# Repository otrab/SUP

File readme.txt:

Readme

Current on HDMI 5v line
http://forum.xda-developers.com/showthread.php?t=2384480

HDMI specification
https://en.wikipedia.org/wiki/HDMI
http://www.hdmi.org/installers/insidehdmicable.aspx

Great ideas
http://forum.arduino.cc/index.php?topic=119879.0
http://articulo.mercadolibre.cl/MLC-432821282-switch-hdmi-hasta-3-dispositivos-1080p-_JM ($4.800)
http://www.aliexpress.com/item/1pc-Switcher-Splitter-Cable-For-HDTV-3-IN-1-OUT-1080P-Hub-V1-4B-HDMI-Switch/32291909706.html

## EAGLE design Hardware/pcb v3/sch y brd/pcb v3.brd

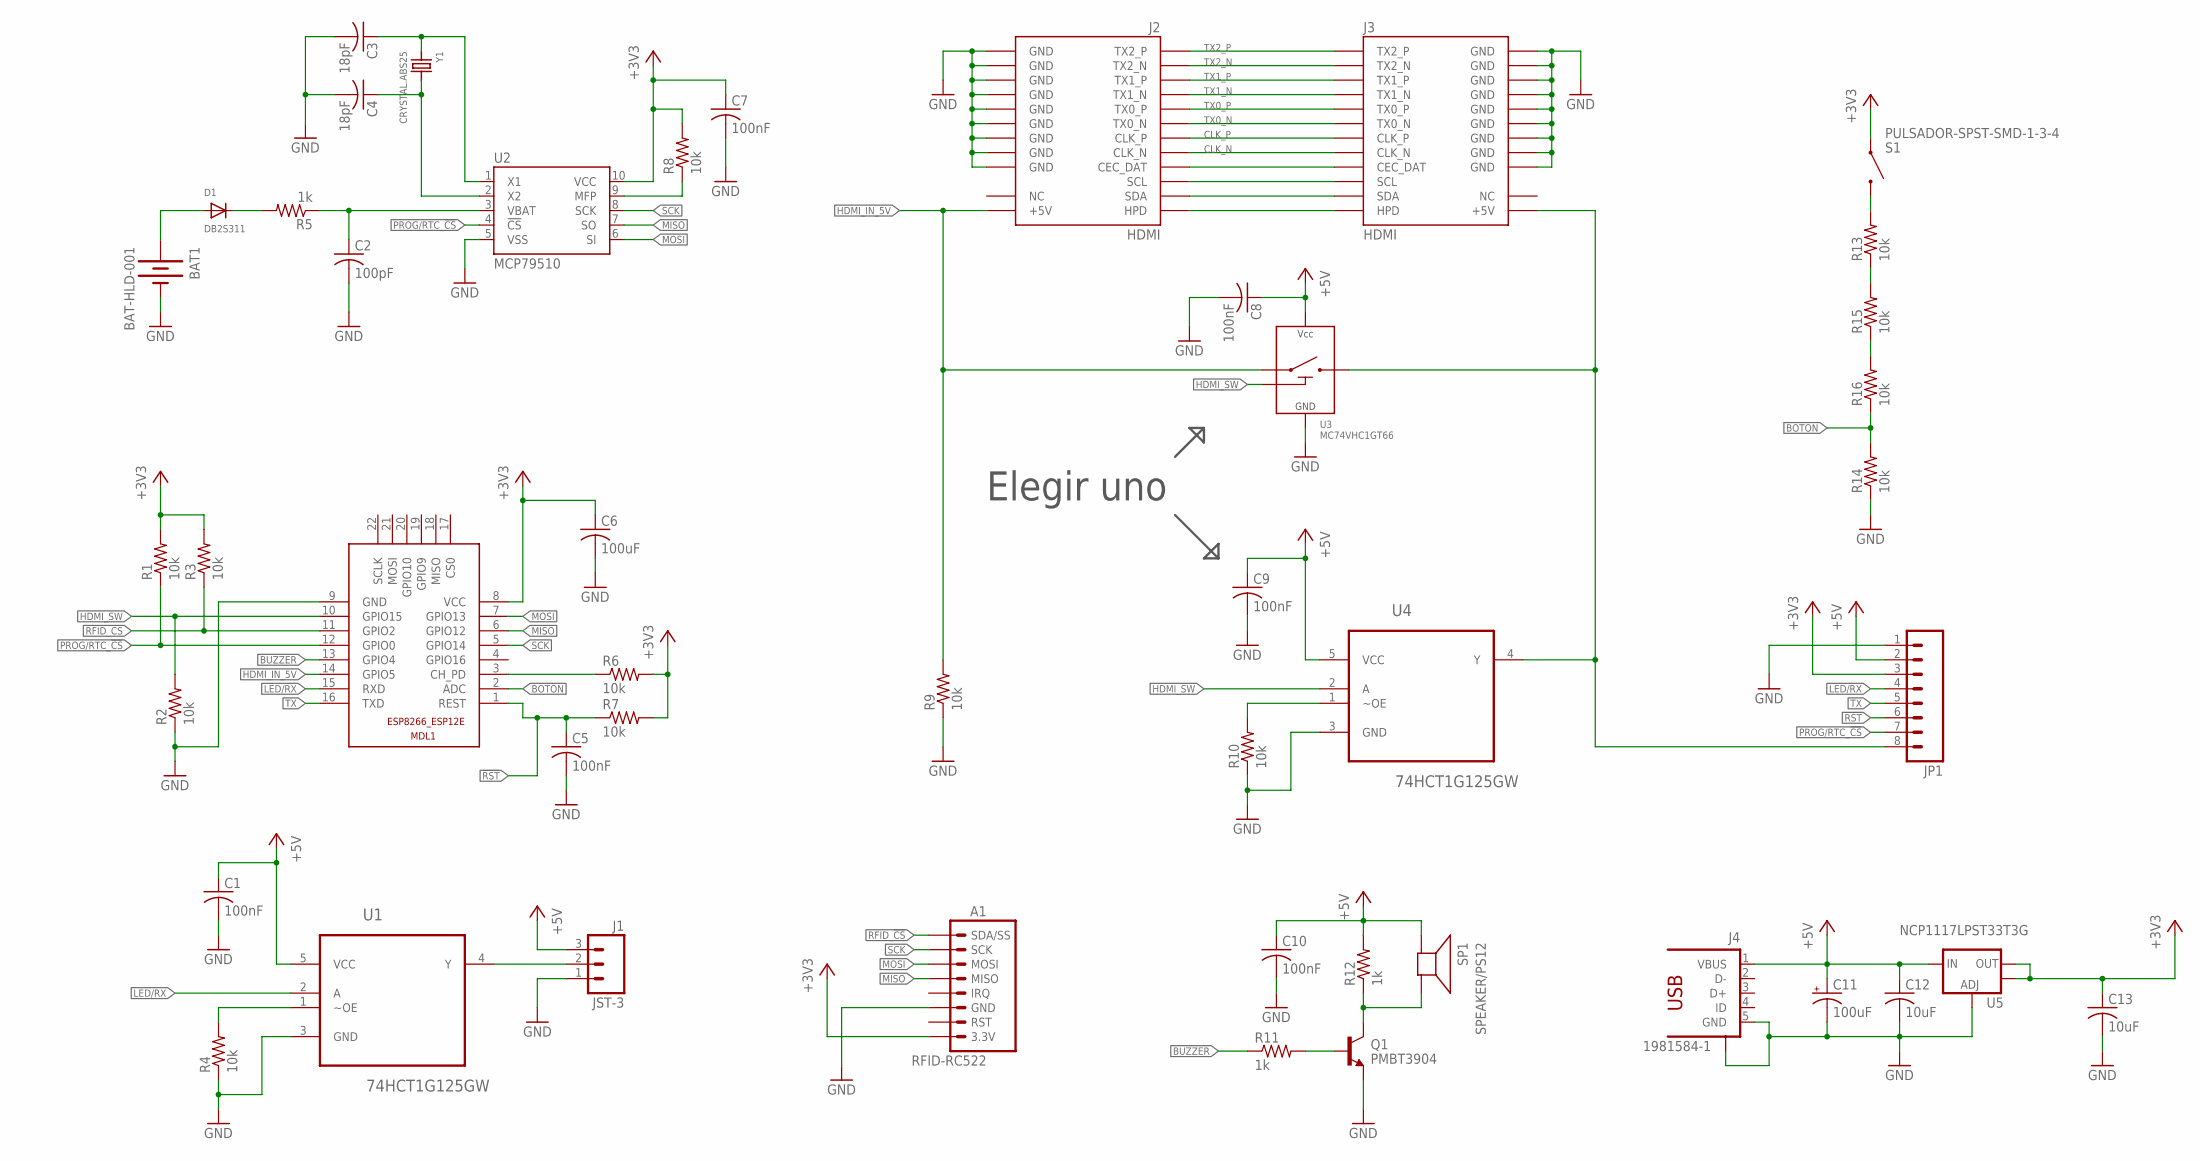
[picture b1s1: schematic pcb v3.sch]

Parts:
A1: RFID-RC522
BAT1: BAT-HLD-001; BATTCON_20MM
C1, C5, C7, C8, C9, C10: 100nF; C0805
C2: 100pF; C0805
C3, C4: 18pF; C0805
C6: 100uF; C1206
C11: 100uF; UD-6,3X5,8_NICHICON_LPADS
C12, C13: 10uF; C0805
D1: DB2S311; SOD-523
J1: JST-3; B3B-PH-SM4-TB
J2, J3: HDMI; 0471511071
J4: 1981584-1
JP1: M081X08; 1X08
MDL1: ESP8266-12EESP8266-ESP12E; ESP8266-ESP12E
Q1: PMBT3904; SOT-23-3
R1, R2, R3, R4, R6, R7, R8, R9, R10, R13, R14, R15, R16: 10k; R0805
R5, R11, R12: 1k; R0805
S1: PULSADOR-SPST-SMD-1-3-4; PTS645SM43SMTR92
SP1: SPEAKER/PS12; PS12
U1, U4: 74HCT1G125GW; SOT65P210X110-5N
U2: MCP79510; MSOP10
U3: MC74VHC1GT66; TSOP-5
U5: NCP1117LPST33T3G; SOT223
Y1: CRYSTAL.ABS25; ABS25

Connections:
!RST: C5.1, JP1.6, MDL1.1 (REST), R7.1
+3V3: A1.3.3V, C6.1, C7.1, C13.1, JP1.3, MDL1.8 (VCC), R1.2, R3.2, R6.2, R7.2, R8.2, S1.P$1, U2.10 (VCC), U5.2 (OUT), U5.4 (OUT)
+5V: C1.1, C8.1, C9.1, C10.1, C11.+, C12.1, J1.3, J4.1 (VBUS), JP1.2, R12.2, SP1.P$1 (+), U1.5 (VCC), U3.5, U4.5 (VCC), U5.3 (IN)
BOTON: MDL1.2 (ADC), R14.2, R16.1
BUZZER: MDL1.13 (GPIO4), R11.1
CLK_N: J2.P$12 (CLK_N), J3.P$12 (CLK_N)
CLK_P: J2.P$10 (CLK_P), J3.P$10 (CLK_P)
GND: A1.GND, BAT1.2 (-), C1.2, C2.2, C3.2, C4.2, C5.2, C6.2, C7.2, C8.2, C9.2, C10.2, C11.-, C12.2, C13.2, J1.1, J2.P$2 (GND), J2.P$5 (GND), J2.P$8 (GND), J2.P$11 (GND), J2.P$17 (GND), J2.P$20 (GND), J2.P$21 (GND), J2.P$22 (GND), J2.P$23 (GND), J3.P$2 (GND), J3.P$5 (GND), J3.P$8 (GND), J3.P$11 (GND), J3.P$17 (GND), J3.P$20 (GND), J3.P$21 (GND), J3.P$22 (GND), J3.P$23 (GND), J4.5 (GND), J4.S1, J4.S2, J4.S3, J4.S4, JP1.1, MDL1.9 (GND), Q1.2 (E), R2.1, R4.1, R9.1, R10.1, R14.1, U1.3 (GND), U2.5 (VSS), U3.3, U4.3 (GND), U5.1 (ADJ)
HDMI_IN_5V: J2.P$18 (+5V), MDL1.14 (GPIO5), R9.2, U3.1
HDMI_OUT_5V: J3.P$18 (+5V), JP1.8, U3.2, U4.4 (Y)
HDMI_SW: MDL1.10 (GPIO15), R2.2, U3.4, U4.2 (A)
LED/RX: JP1.4, MDL1.15 (RXD), U1.2 (A)
MISO: A1.MISO, MDL1.6 (GPIO12), U2.7 (SO)
MOSI: A1.MOSI, MDL1.7 (GPIO13), U2.6 (SI)
unnamed: Q1.1 (B), R11.2
unnamed: C3.1, U2.1 (X1), Y1.1
unnamed: C4.1, U2.2 (X2), Y1.4 (2)
unnamed: R4.2, U1.1 (~OE)
unnamed: Q1.3 (C), R12.1, SP1.P$2 (-)
unnamed: R8.1, U2.9 (MFP)
unnamed: BAT1.1 (+), D1.A
unnamed: D1.K (C), R5.2
unnamed: C2.1, R5.1, U2.3 (VBAT)
unnamed: MDL1.3 (CH_PD), R6.1
unnamed: J1.2, U1.4 (Y)
unnamed: R13.2, S1.P$3, S1.P$4
unnamed: R13.1, R15.2
unnamed: R15.1, R16.2
unnamed: R10.2, U4.1 (~OE)
unnamed: J2.P$13 (CEC_DAT), J3.P$13 (CEC_DAT)
unnamed: J2.P$15 (SCL), J3.P$15 (SCL)
unnamed: J2.P$16 (SDA), J3.P$16 (SDA)
unnamed: J2.P$19 (HPD), J3.P$19 (HPD)
PROG/RTC_!CS: JP1.7, MDL1.12 (GPIO0), R1.1, U2.4 (!CS)
RFID_!CS: A1.SDA (SDA/SS), MDL1.11 (GPIO2), R3.1
SCK: A1.SCK, MDL1.5 (GPIO14), U2.8 (SCK)
TX: JP1.5, MDL1.16 (TXD)
TX0_N: J2.P$9 (TX0_N), J3.P$9 (TX0_N)
TX0_P: J2.P$7 (TX0_P), J3.P$7 (TX0_P)
TX1_N: J2.P$6 (TX1_N), J3.P$6 (TX1_N)
TX1_P: J2.P$4 (TX1_P), J3.P$4 (TX1_P)
TX2_N: J2.P$3 (TX2_N), J3.P$3 (TX2_N)
TX2_P: J2.P$1 (TX2_P), J3.P$1 (TX2_P)

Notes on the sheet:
Elegir uno

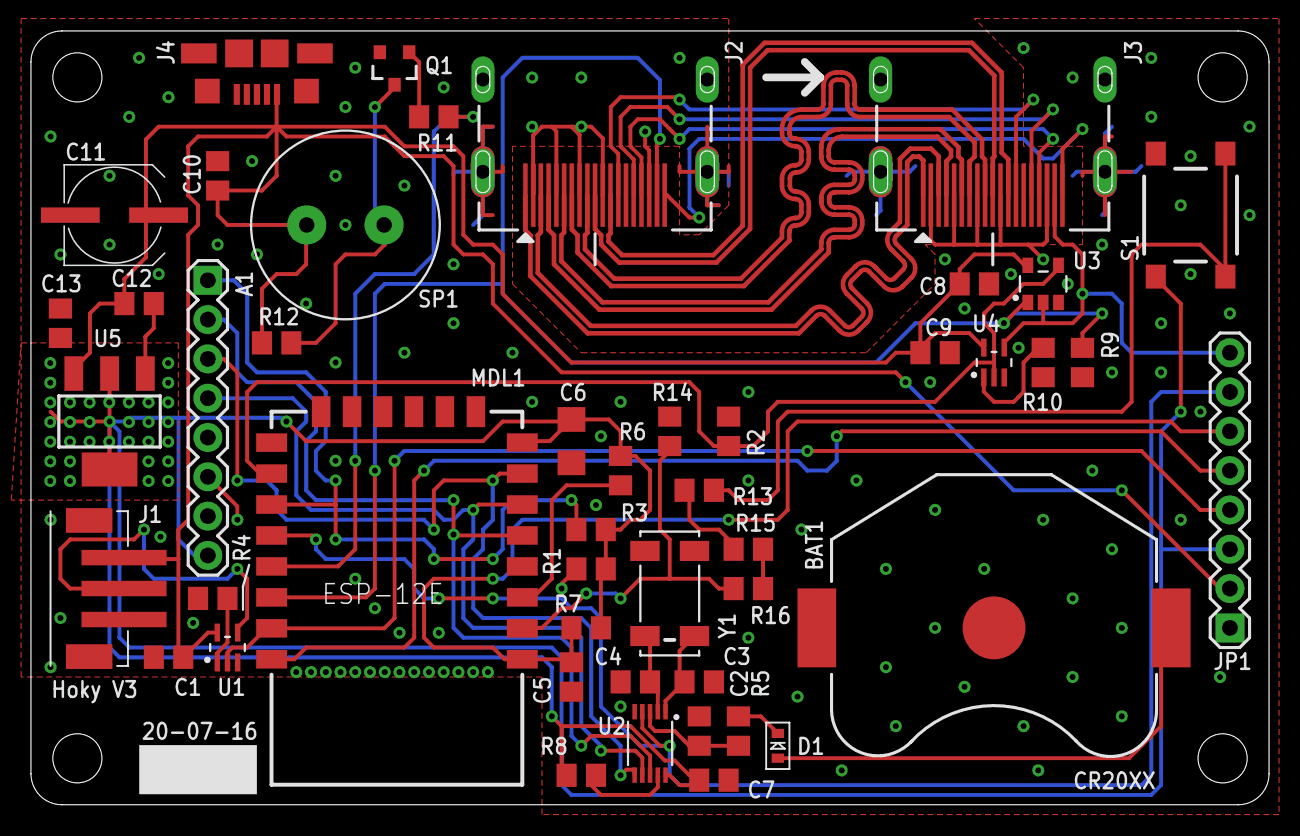
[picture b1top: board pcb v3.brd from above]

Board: 2 copper layers, 80.0 x 50.0 mm, 47 parts (0 on the bottom side), 43 nets.

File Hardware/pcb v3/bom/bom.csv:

"Qty";"Value";"Device";"Package";"Parts";"Description";"";
"1";"";"ESP8266-12EESP8266-ESP12E";"ESP8266-ESP12E";"MDL1";"ESP8266-12E with additional I/O and GPIO04/05 corrected";"";
"1";"";"M07";"1X07";"JP1";"Header 7";"";
"6";"100nF";"C-USC0805";"C0805";"C1, C5, C7, C8, C9, C10";"CAPACITOR, American symbol";"";
"1";"100pF";"C-USC0805";"C0805";"C2";"CAPACITOR, American symbol";"";
"1";"100uF";"C-USC1206";"C1206";"C6";"CAPACITOR, American symbol";"";
"14";"10k";"R-US_R0805";"R0805";"R1, R2, R3, R4, R6, R7, R8, R9, R10, R13, R14, R15, R16, R17";"RESISTOR, American symbol";"";
"2";"10uF";"C-USC0805";"C0805";"C12, C13";"CAPACITOR, American symbol";"";
"1";"1200uF";"CPOL-USUD-10X10";"UD-10X10_NICHICON";"C11";"POLARIZED CAPACITOR, American symbol";"";
"2";"18pF";"C-USC0805";"C0805";"C3, C4";"CAPACITOR, American symbol";"";
"1";"1981584-1";"1981584-1";"1981584-1";"J4";"Receptacle, micro-USB, type A/B";"";
"3";"1k";"R-US_R0805";"R0805";"R5, R11, R12";"RESISTOR, American symbol";"";
"2";"74HCT1G125GW";"74HCT1G125GW";"SOT65P210X110-5N";"U1, U4";"Bus buffer/line driver";"";
"1";"BAT-HLD-001";"LINX-BAT-HLD-00120SMD";"BATTCON_20MM";"BAT1";"Battery Holders";"";
"1";"CRYSTAL.ABS25";"CRYSTAL.ABS25";"ABS25";"Y1";"";"";
"1";"DB2S311";"DIODESOD-523";"SOD-523";"D1";"Diode";"";
"2";"HDMI";"HDMI";"0471511071";"J2, J3";"";"";
"1";"JST-3";"JST-3";"B3B-PH-SM4-TB";"J1";"";"";
"1";"MC74VHC1GT66";"MC74VHC1GT66";"TSOP-5";"U3";"";"";
"1";"MCP79510";"MCP79510";"MSOP10";"U2";"";"";
"1";"NCP1117LPST33T3G";"V_REG_LM1117SOT223";"SOT223";"U5";"Voltage Regulator LM1117";"";
"1";"PMBT3904";"PMBT3904";"SOT-23-3";"Q1";"PMBT3904";"";
"1";"PULSADOR-SPST-SMD-1-3-4";"PULSADOR-SPST-SMD-1-3-4";"PTS645SM43SMTR92";"S1";"";"";
"1";"RFID-RC522";"RFID-RC522";"RFID-RC522";"A1";"";"";
"1";"SPEAKER/PS12";"SPEAKER/PS12";"PS12";"SP1";"SPEAKER Source: BuerklinAdded PS12 (for part # PS1240 piezo) http://www.ladyada.net/library/pcb/eaglelibrary.html";"";

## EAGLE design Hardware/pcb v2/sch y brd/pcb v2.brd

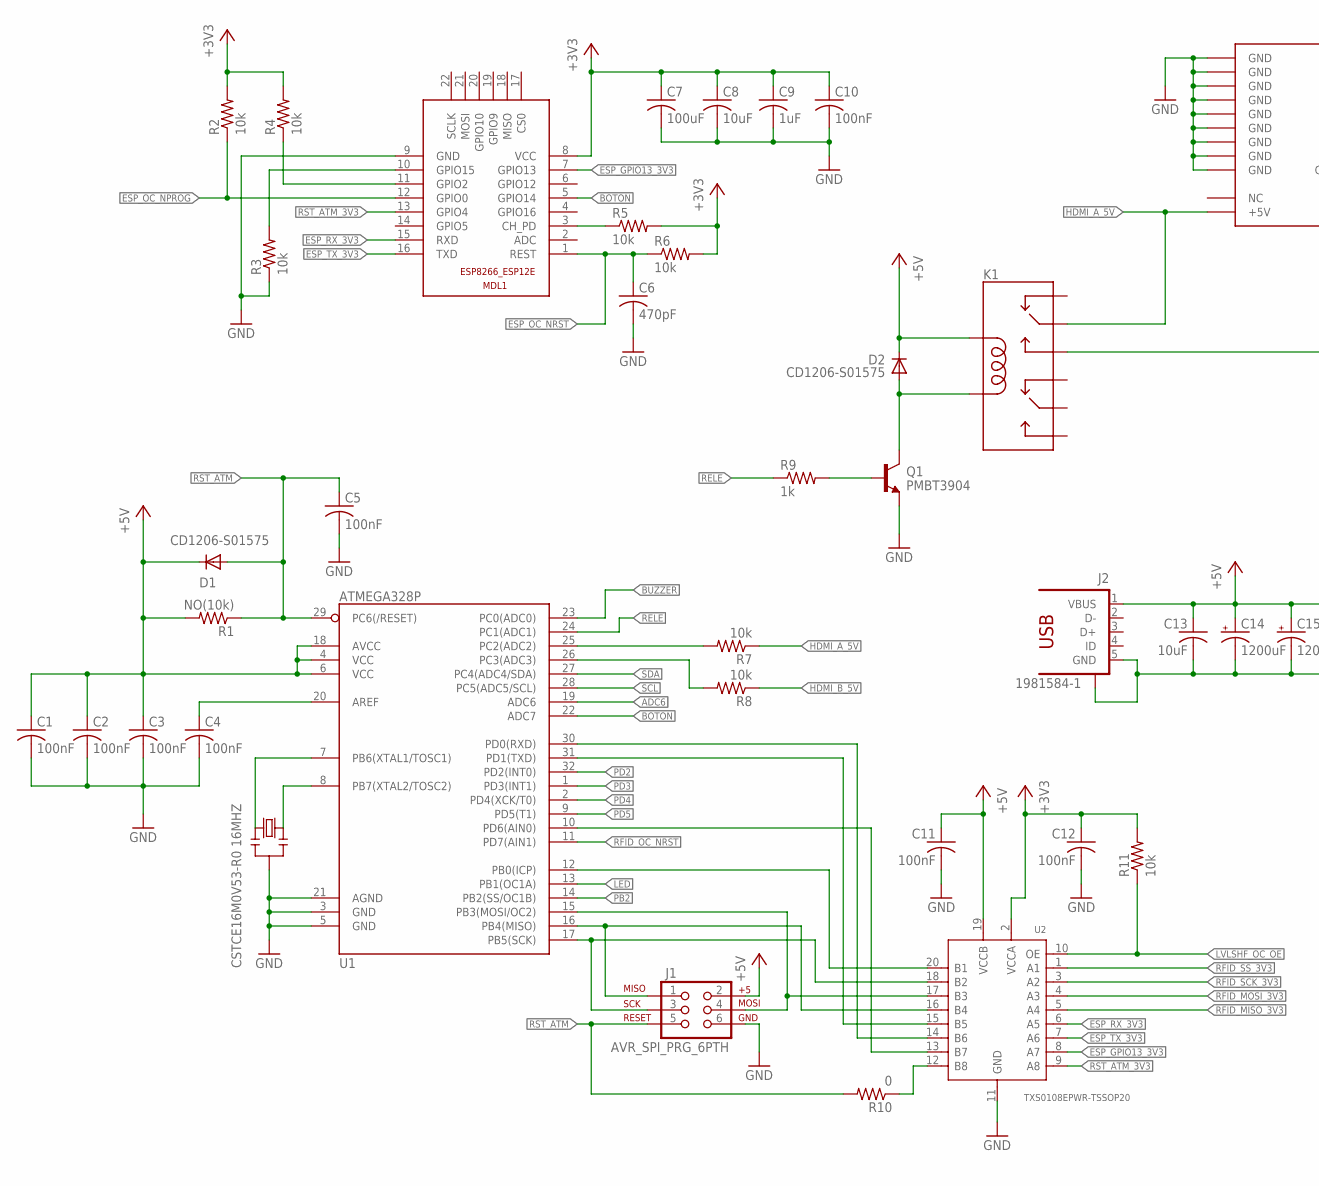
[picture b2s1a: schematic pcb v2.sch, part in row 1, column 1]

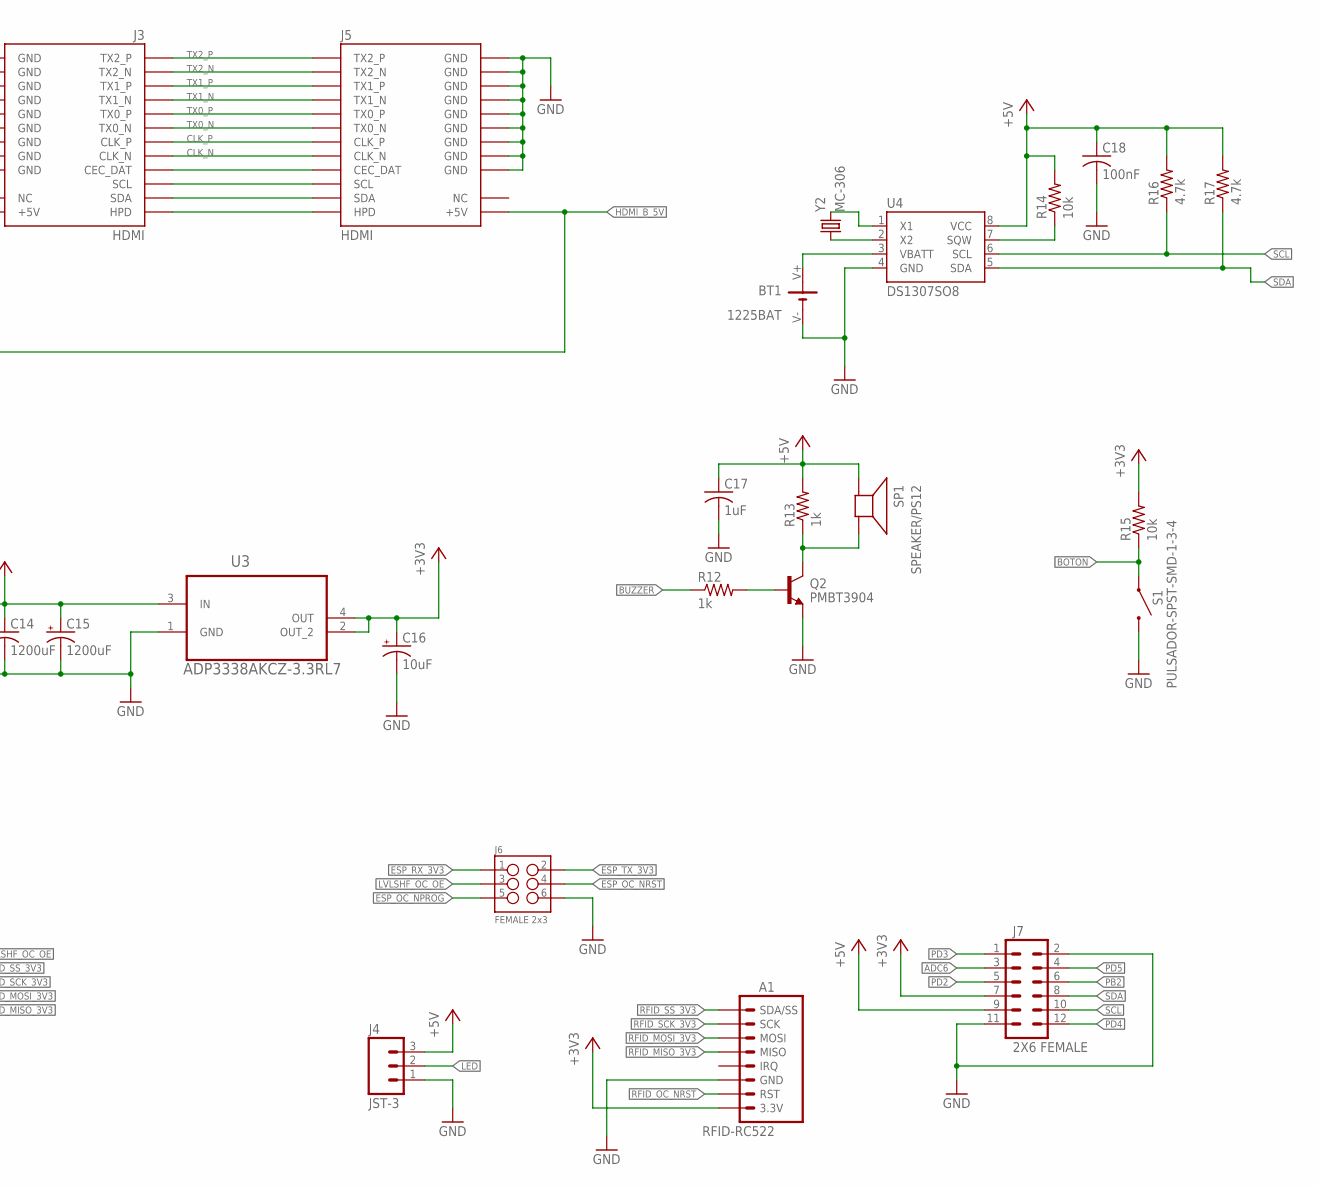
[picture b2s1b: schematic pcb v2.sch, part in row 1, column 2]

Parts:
A1: RFID-RC522
BT1: 1225BAT; BHSD-1225-SM
C1, C2, C3, C4, C5, C10, C11, C12, C18: 100nF; C0603
C6: 470pF; C0603
C7: 100uF; C1206
C8, C13: 10uF; C0805
C9, C17: 1uF; C0805
C14, C15: 1200uF; UD-10X10_NICHICON
C16: 10uF; UD-5X5,8_NICHICON
D1, D2: CD1206-S01575; MINIMELF
J1: AVR_SPI_PRG_6PTH; 2X3
J2: 1981584-1
J3, J5: HDMI; 0471511071
J4: JST-3; B3B-PH-SM4-TB
J6: FEMALE 2x3; 2X3
J7: 2X6 FEMALE; 2X6
K1: RELAY_EE2; RELAY-EE2
MDL1: ESP8266-12EESP8266-ESP12E; ESP8266-ESP12E
Q1, Q2: PMBT3904; SOT-23-3
R1: NO(10k); R0805
R2, R3, R4, R5, R6, R7, R8, R11, R14, R15: 10k; R0603
R9, R12, R13: 1k; R0805
R10: 0; R0805
R16, R17: 4.7k; R0603
S1: PULSADOR-SPST-SMD-1-3-4; PTS645SM43SMTR92
SP1: SPEAKER/PS12; PS12
U1: ATMEGA328P; TQFP32-08
U2: TXS0108EPWR-TSSOP20; TSSOP20-0.65-6.5X4.4MM
U3: ADP3338AKCZ-3.3RL7; SOT230P700X180-4N
U4: DS1307SO8; SO08
Y1: CSTCE16M0V53-R0 16MHZ; RESONATOR
Y2: MC-306

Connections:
+3V3: A1.3.3V, C7.1, C8.1, C9.1, C10.1, C12.1, C16.+, J7.7, MDL1.8 (VCC), R2.2, R4.2, R5.2, R6.2, R11.2, R15.2, U2.2 (VCCA), U3.2 (OUT_2), U3.4 (OUT)
+5V: C1.1, C2.1, C3.1, C11.1, C13.1, C14.+, C15.+, C17.1, C18.1, D1.C, D2.C, J1.2, J2.1 (VBUS), J4.3, J7.9, K1.1 (COIL+), R1.2, R13.2, R14.2, R16.2, R17.2, SP1.P$1 (+), U1.4 (VCC), U1.6 (VCC), U1.18 (AVCC), U2.19 (VCCB), U3.3 (IN), U4.8 (VCC)
ADC6: J7.3, U1.19 (ADC6)
BOTON: MDL1.5 (GPIO14), R15.1, S1.P$1, U1.22 (ADC7)
BUZZER: R12.1, U1.23 (PC0(ADC0))
CLK_N: J3.P$12 (CLK_N), J5.P$12 (CLK_N)
CLK_P: J3.P$10 (CLK_P), J5.P$10 (CLK_P)
ESP_GPIO13_3V3: MDL1.7 (GPIO13), U2.8 (A7)
ESP_OC_NPROG: J6.5, MDL1.12 (GPIO0), R2.1
ESP_OC_NRST: C6.1, J6.4, MDL1.1 (REST), R6.1
ESP_RX_3V3: J6.1, MDL1.15 (RXD), U2.6 (A5)
ESP_TX_3V3: J6.2, MDL1.16 (TXD), U2.7 (A6)
GND: A1.GND, BT1.V-, C1.2, C2.2, C3.2, C4.2, C5.2, C6.2, C7.2, C8.2, C9.2, C10.2, C11.2, C12.2, C13.2, C14.-, C15.-, C16.-, C17.2, C18.2, J1.6, J2.5 (GND), J2.S1, J2.S2, J2.S3, J2.S4, J3.P$2 (GND), J3.P$5 (GND), J3.P$8 (GND), J3.P$11 (GND), J3.P$17 (GND), J3.P$20 (GND), J3.P$21 (GND), J3.P$22 (GND), J3.P$23 (GND), J4.1, J5.P$2 (GND), J5.P$5 (GND), J5.P$8 (GND), J5.P$11 (GND), J5.P$17 (GND), J5.P$20 (GND), J5.P$21 (GND), J5.P$22 (GND), J5.P$23 (GND), J6.6, J7.2, J7.11, MDL1.9 (GND), Q1.2 (E), Q2.2 (E), R3.1, S1.P$3, S1.P$4, U1.3 (GND), U1.5 (GND), U1.21 (AGND), U2.11 (GND), U3.1 (GND), U4.4 (GND), Y1.2
HDMI_A_5V: J3.P$18 (+5V), K1.4 (MAIN1), R7.1
HDMI_B_5V: J5.P$18 (+5V), K1.5 (OFF1), R8.1
LED: J4.2, U1.13 (PB1(OC1A))
LVLSHF_OC_OE: J6.3, R11.1, U2.10 (OE)
unnamed: Q2.1 (B), R12.2
unnamed: U4.1 (X1), Y2.4 (2)
unnamed: U4.2 (X2), Y2.1
unnamed: U1.8 (PB7(XTAL2/TOSC2)), Y1.3
unnamed: Q2.3 (C), R13.1, SP1.P$2 (-)
unnamed: R14.1, U4.7 (SQW)
unnamed: R10.1, U2.12 (B8)
unnamed: U1.12 (PB0(ICP)), U2.20 (B1)
unnamed: BT1.V+, U4.3 (VBATT)
unnamed: MDL1.3 (CH_PD), R5.1
unnamed: U1.7 (PB6(XTAL1/TOSC1)), Y1.1
unnamed: MDL1.11 (GPIO2), R4.1
unnamed: C4.1, U1.20 (AREF)
unnamed: D2.A, K1.12 (COIL-), Q1.3 (C)
unnamed: MDL1.10 (GPIO15), R3.2
unnamed: J1.3, U1.17 (PB5(SCK)), U2.18 (B2)
unnamed: J1.1, U1.16 (PB4(MISO)), U2.16 (B4)
unnamed: J1.4, U1.15 (PB3(MOSI/OC2)), U2.17 (B3)
unnamed: Q1.1 (B), R9.2
unnamed: U1.30 (PD0(RXD)), U2.14 (B6)
unnamed: U1.31 (PD1(TXD)), U2.15 (B5)
unnamed: J3.P$13 (CEC_DAT), J5.P$13 (CEC_DAT)
unnamed: J3.P$15 (SCL), J5.P$15 (SCL)
unnamed: J3.P$16 (SDA), J5.P$16 (SDA)
unnamed: J3.P$19 (HPD), J5.P$19 (HPD)
unnamed: R7.2, U1.25 (PC2(ADC2))
unnamed: R8.2, U1.26 (PC3(ADC3))
unnamed: U1.10 (PD6(AIN0)), U2.13 (B7)
PB2: J7.6, U1.14 (PB2(SS/OC1B))
PD2: J7.5, U1.32 (PD2(INT0))
PD3: J7.1, U1.1 (PD3(INT1))
PD4: J7.12, U1.2 (PD4(XCK/T0))
PD5: J7.4, U1.9 (PD5(T1))
RELE: R9.1, U1.24 (PC1(ADC1))
RFID_MISO_3V3: A1.MISO, U2.5 (A4)
RFID_MOSI_3V3: A1.MOSI, U2.4 (A3)
RFID_OC_NRST: A1.RST, U1.11 (PD7(AIN1))
RFID_SCK_3V3: A1.SCK, U2.3 (A2)
RFID_SS_3V3: A1.SDA (SDA/SS), U2.1 (A1)
RST_ATM: C5.1, D1.A, J1.5, R1.1, R10.2, U1.29 (PC6(/RESET))
RST_ATM_3V3: MDL1.13 (GPIO4), U2.9 (A8)
SCL: J7.10, R16.1, U1.28 (PC5(ADC5/SCL)), U4.6 (SCL)
SDA: J7.8, R17.1, U1.27 (PC4(ADC4/SDA)), U4.5 (SDA)
TX0_N: J3.P$9 (TX0_N), J5.P$9 (TX0_N)
TX0_P: J3.P$7 (TX0_P), J5.P$7 (TX0_P)
TX1_N: J3.P$6 (TX1_N), J5.P$6 (TX1_N)
TX1_P: J3.P$4 (TX1_P), J5.P$4 (TX1_P)
TX2_N: J3.P$3 (TX2_N), J5.P$3 (TX2_N)
TX2_P: J3.P$1 (TX2_P), J5.P$1 (TX2_P)

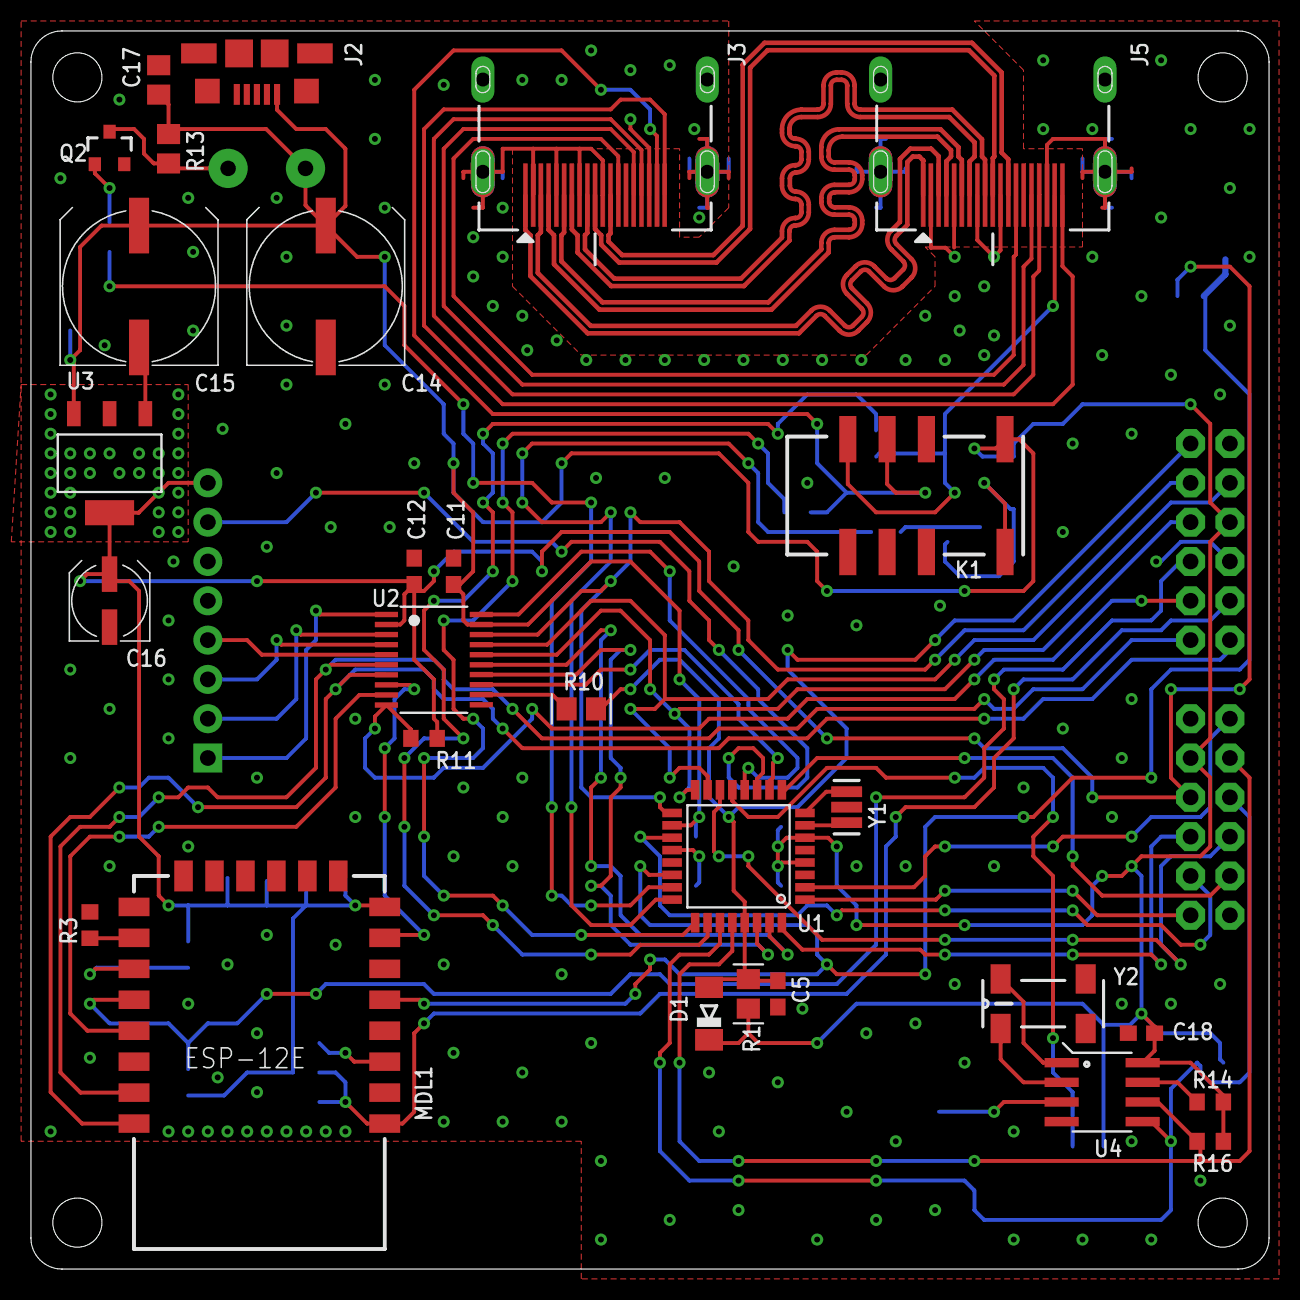
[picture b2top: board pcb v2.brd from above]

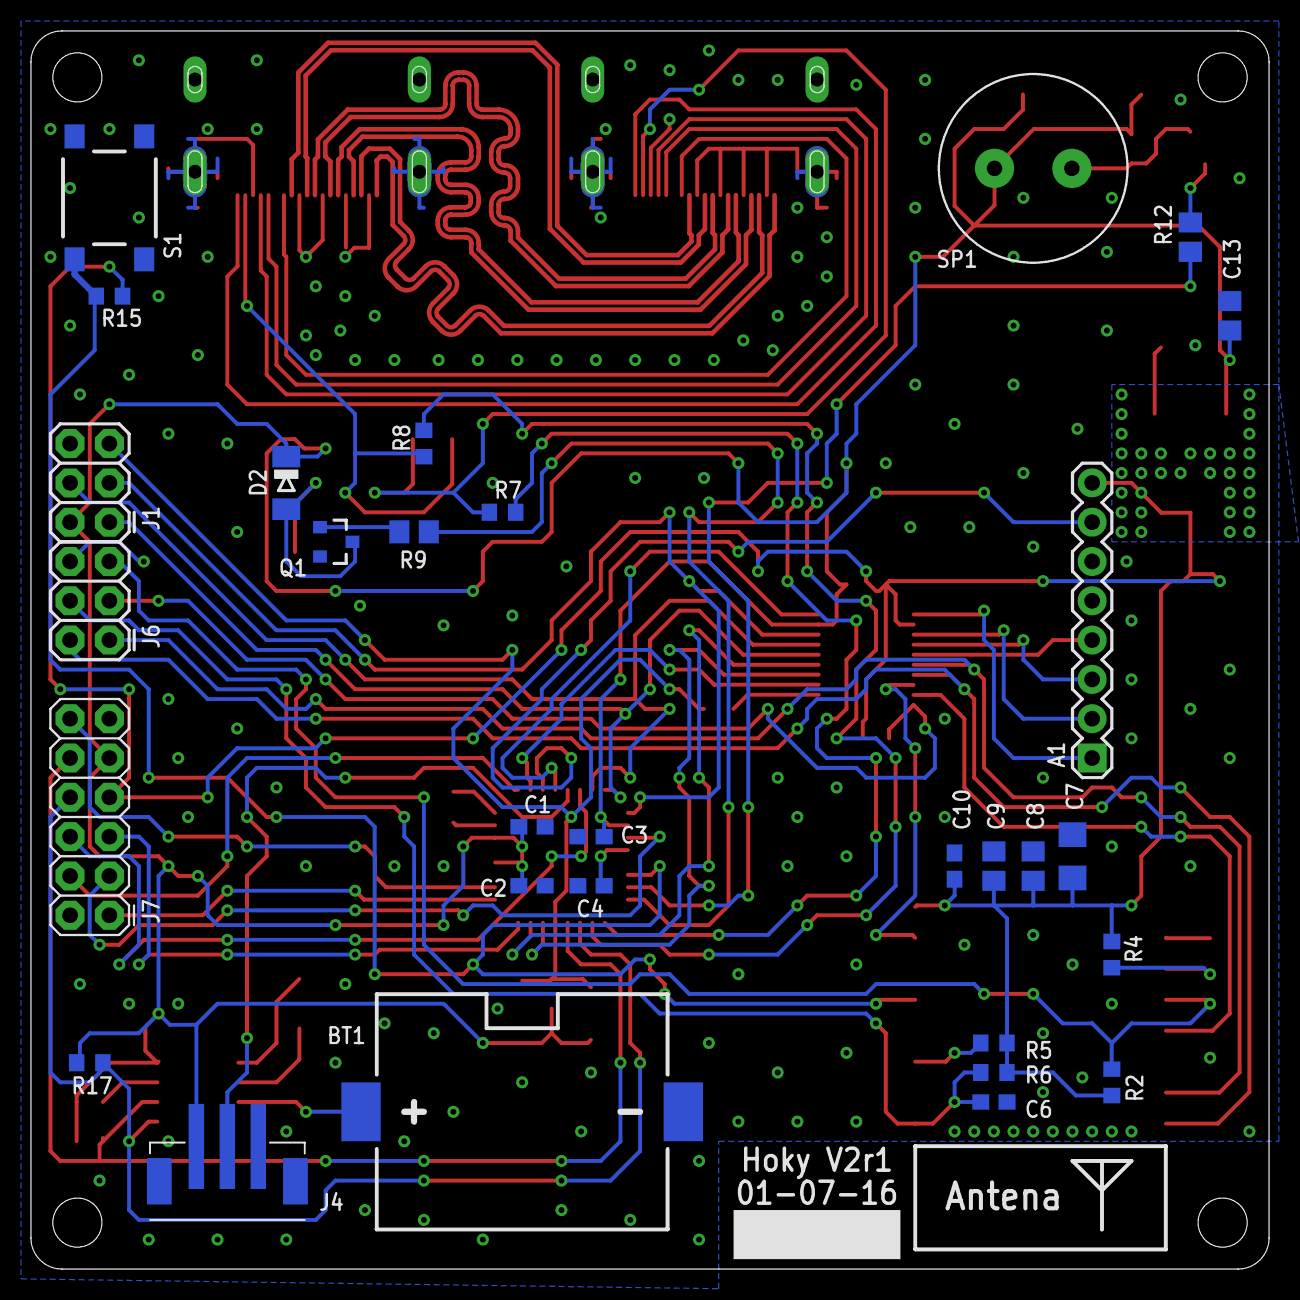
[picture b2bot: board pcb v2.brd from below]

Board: 2 copper layers, 80.0 x 80.0 mm, 58 parts (30 on the bottom side), 66 nets.

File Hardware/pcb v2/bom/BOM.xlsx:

Qty | Value | Device | Package | Parts | Fabricante | Codigo fabricante | Codigo digikey | Description | Alto
1 |  | ESP8266-12EESP8266-ESP12E | ESP8266-ESP12E | MDL1 |  |  |  | ESP8266-12E with additional I/O and GPIO04/05 corrected
1 |  | RELAY_EE2 | RELAY-EE2 | K1 | Kemet | EE2-5NU | 399-11056-5-ND | Rele smd | 10mm
1 | 0R | R-US_R0805 | R0805 | R10 |  |  | 1276-5466-1-ND | RESISTOR, American symbol
10 | 100nF | C-USC0603 | C0603 | C1, C2, C3, C4, C5, C10, C11, C12, C18, C6 |  |  | 1276-1005-1-ND | CAPACITOR, American symbol
1 | 100uF | C-USC1206 | C1206 | C7 |  | TL8A0107M010C | 718-1921-1-ND | CAPACITOR, American symbol
10 | 10k | R-US_R0603 | R0603 | R2, R3, R4, R5, R6, R7, R8, R11, R14, R15 |  |  | 311-10KGRCT-ND | RESISTOR, American symbol
2 | 10uF | C-USC0805 | C0805 | C8, C13 |  |  | 490-10516-1-ND | CAPACITOR, American symbol
1 | 10uF | CPOL-USUD-5X5,8 | UD-5X5,8_NICHICON | C16 | Nichicon | UCD1V100MCL1GS | 493-6418-1-ND | Condensador electrolitico
2 | 1200uF | CPOL-USUD-10X10 | UD-10X10_NICHICON | C14, C15 | United Chemi-Con | EMZJ100ADA122MJA0G | 565-3654-1-ND | Condensador electrolitico | 10.30mm
1 | 1225BAT | 1225BAT | BHSD-1225-SM | BT1 | MPD (Memory Protection Devices) | BHSD-1225-SM | BHSD-1225-SMCT-ND | Vertical battery holder
1 | 1981584-1 | 1981584-1 | 1981584-1 | J2 | TE Connectivity AMP Connectors | 1981584-1 | A97799CT-ND | Receptacle, micro-USB, type A/B
3 | 1k | R-US_R0805 | R0805 | R9, R12, R13 |  |  | RMCF0805JT1K00CT-ND | RESISTOR, American symbol
2 | 1uF | C-USC0805 | C0805 | C9, C17 |  |  | 1276-1275-1-ND | CAPACITOR, American symbol
2 | 2X6 MALE | M06X2PTH_FEMALE | 2X6 | J7, J1, J6 | Harwin Inc. | M20-9980646 | 952-2126-ND | Pin header 0.1" 2x6 puerto expansion y AVR-ISP + ESP
2 | 4.7k | R-US_R0603 | R0603 | R16, R17 |  |  | 311-4.7KGRCT-ND | RESISTOR, American symbol
1 | ADP3338AKCZ-3.3RL7 | ADP3338AKCZ-3.3RL7 | SOT230P700X180-4N | U3 | Analog Devices Inc. | ADP3338AKCZ-3.3RL7 | ADP3338AKCZ-3.3RL7CT-ND | Low Dropout Regulator
1 | ATMEGA328P | ATMEGA328_SMT | TQFP32-08 | U1 | Atmel | ATMEGA328P-AU | ATMEGA328P-AU-ND | 32-Pin Atmega328 part
2 | CD1206-S01575 | DIODE-MINIMELF | MINIMELF | D1, D2 | Bourns Inc. | CD1206-S01575 | CD1206-S01575CT-ND | DIODE
1 | CSTCE16M0V53-R0 16MHZ | RESONATORMU | RESONATOR | Y1 | Murata Electronics | CSTCE16M0V53-R0 | 490-1198-1-ND | Resonador 16mhz
1 | DS1307SO8 | DS1307SO8 | SO08 | U4 | Maxim Integrated | DS1307Z+T&R | DS1307Z+T&RCT-ND | I2C real-time clock with battery backup.
2 | HDMI | HDMI | 471511071 | J3, J5 | Molex, LLC | 471511071 | WM7083CT-ND | HDMI
1 | JST-3 | JST-3 | B3B-PH-SM4-TB | J4 | JST Sales America Inc. | B3B-PH-SM4-TB(LF)(SN) | 455-1735-1-ND | Conector jst para leds
1 | MC-306 | MC-306 | MC-306 | Y2 | EPSON | MC-306 32.7680K-A0:ROHS | SER2407CT-ND | kHz RANGE CRYSTAL UNIT SMD
2 | PMBT3904 | PMBT3904 | SOT-23-3 | Q1, Q2 |  |  | 568-1741-1-ND | NPN BJT
0.2 | RFID-RC522 | RFID-RC522 | RFID-RC522 | A1 | TE Connectivity AMP Connectors | 9-146462-0 | A122005-ND | Pines board to board 0.1", vienen de a 40 | 7.62mm
1 | SPEAKER/PS12 | SPEAKER/PS12 | PS12 | SP1 | TDK Corporation | PS1240P02BT | 445-2525-1-ND | Buzzer piezo electrico | 6.5mm
1 | TXS0108EPWR-TSSOP20 | LOGIC-TXS0108EPWR(TSSOP20) | TSSOP20-0.65-6.5X4.4MM | U2 | Texas Instruments | TXS0108EPWR | 296-23011-1-ND | Level shifter bidireccional con direccion automatica
Notas: | Los condensadores ceramicos se elijieron con dielectrico X7R en lo posible
 | Todos los condensadores tienen rated voltage mayor o igual a 10V

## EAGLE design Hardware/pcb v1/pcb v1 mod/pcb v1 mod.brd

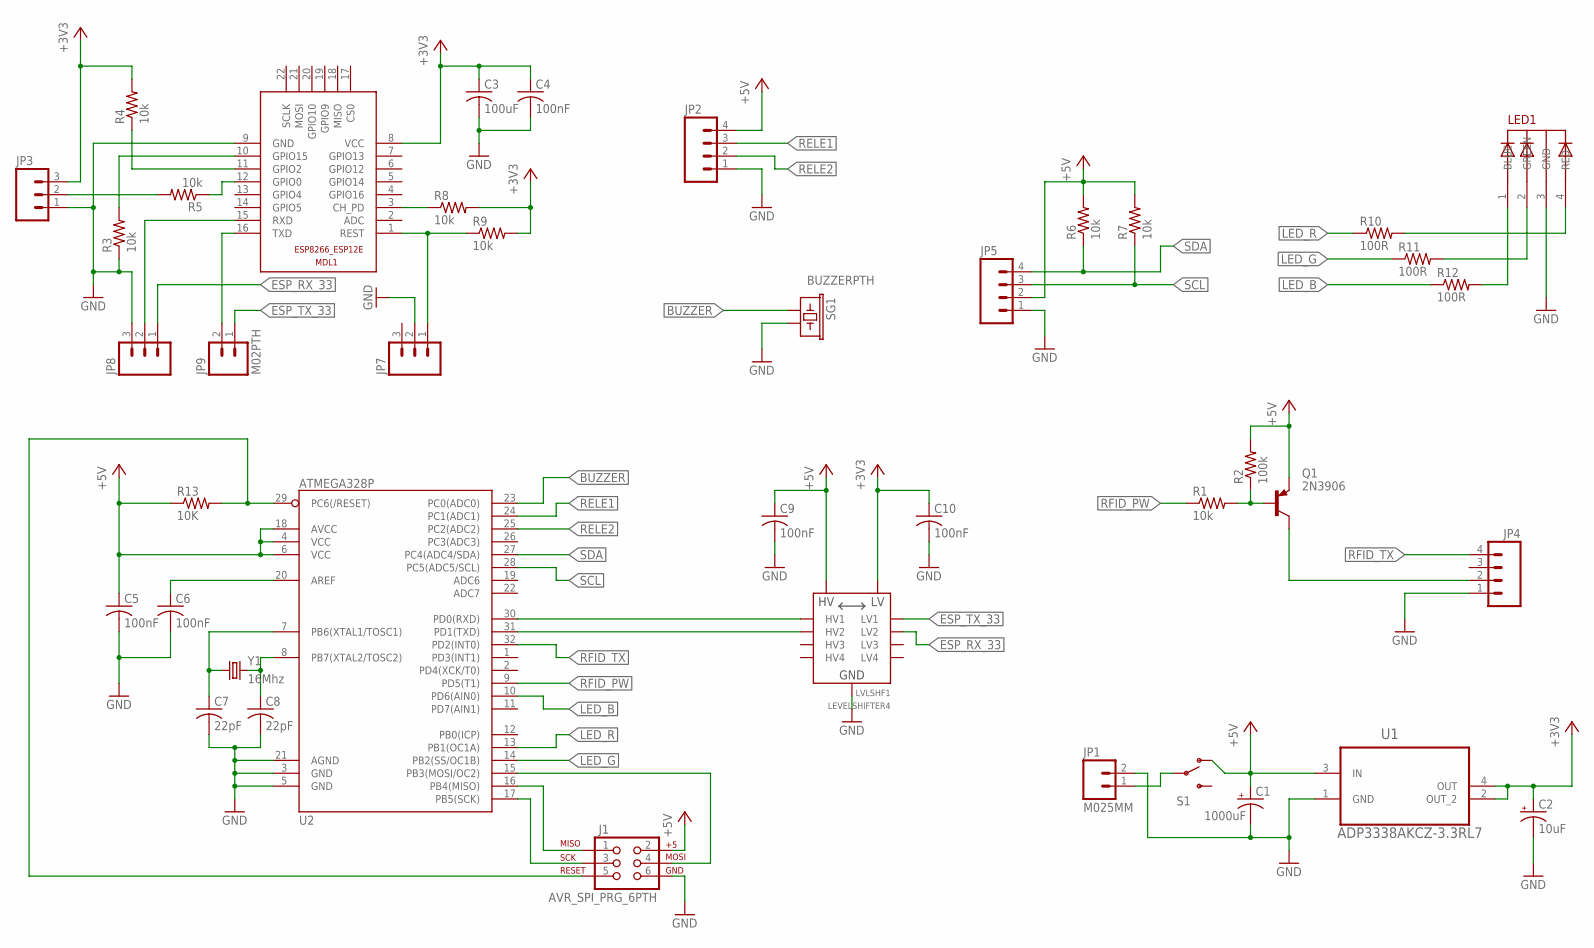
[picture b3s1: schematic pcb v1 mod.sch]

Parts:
C1: 1000uF; E2,5-6
C2: 10uF; E2,5-6
C3: 100uF; C1206
C4, C5, C6, C9, C10: 100nF; C0805
C7, C8: 22pF; C1206
J1: AVR_SPI_PRG_6PTH; 2X3
JP1: M025MM; SCREWTERMINAL-5MM-2
JP2, JP4, JP5: M041X04_NO_SILK; 1X04_NO_SILK
JP3, JP7, JP8: M03PTH; 1X03
JP9: M02PTH; 1X02
LED1: 5MMRGBLED; LED5MMRGB
LVLSHF1: LEVELSHIFTER4
MDL1: ESP8266-12EESP8266-ESP12E; ESP8266-ESP12E
Q1: 2N3906; TO92
R1, R3, R4, R5, R6, R7, R8, R9: 10k; R0805
R2: 100k; R0805
R10: 100R; R1206
R11, R12: 100R; R0805
R13: 10K; R0805
S1: SWITCH-SPDTPTH; SWITCH-SPDT
SG1: BUZZERPTH; BUZZER-12MM
U1: ADP3338AKCZ-3.3RL7; SOT230P700X180-4N
U2: ATMEGA328P; TQFP32-08
Y1: 16Mhz; HC49US

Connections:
+3V3: C2.+, C3.1, C4.1, C10.1, JP3.3, LVLSHF1.LV, MDL1.8 (VCC), R4.2, R8.2, R9.2, U1.2 (OUT_2), U1.4 (OUT)
+5V: C1.+, C5.1, C9.1, J1.2, JP2.4, JP5.2, LVLSHF1.HV, Q1.3 (E), R2.2, R6.2, R7.2, R13.1, S1.1 (O), U1.3 (IN), U2.4 (VCC), U2.6 (VCC), U2.18 (AVCC)
AT_RST: J1.5, R13.2, U2.29 (PC6(/RESET))
BUZZER: SG1.+ (1), U2.23 (PC0(ADC0))
ESP_RX_33: JP8.1, LVLSHF1.LV2
ESP_TX_33: JP9.1, LVLSHF1.LV1
GND: C1.-, C2.-, C3.2, C4.2, C5.2, C6.2, C7.2, C8.2, C9.2, C10.2, J1.6, JP1.2, JP2.1, JP3.1, JP4.1, JP5.1, JP7.2, JP8.3, LED1.3 (GND), LVLSHF1.GND, LVLSHF1.GND1 (GND), MDL1.9 (GND), R3.1, SG1.- (2), U1.1 (GND), U2.3 (GND), U2.5 (GND), U2.21 (AGND)
LED_B: R12.1, U2.10 (PD6(AIN0))
LED_G: R11.1, U2.14 (PB2(SS/OC1B))
LED_R: R10.1, U2.13 (PB1(OC1A))
unnamed: JP1.1, S1.2
unnamed: MDL1.3 (CH_PD), R8.1
unnamed: MDL1.11 (GPIO2), R4.1
unnamed: MDL1.12 (GPIO0), R5.1
unnamed: MDL1.10 (GPIO15), R3.2
unnamed: JP8.2, MDL1.15 (RXD)
unnamed: Q1.2 (B), R1.2, R2.1
unnamed: JP9.2, MDL1.16 (TXD)
unnamed: JP7.1, MDL1.1 (REST), R9.1
unnamed: LED1.4 (RED), R10.2
unnamed: C7.1, U2.7 (PB6(XTAL1/TOSC1)), Y1.1
unnamed: C8.1, U2.8 (PB7(XTAL2/TOSC2)), Y1.2
unnamed: C6.1, U2.20 (AREF)
unnamed: LED1.2 (GREEN), R11.2
unnamed: LED1.1 (BLUE), R12.2
unnamed: J1.3, U2.17 (PB5(SCK))
unnamed: J1.1, U2.16 (PB4(MISO))
unnamed: J1.4, U2.15 (PB3(MOSI/OC2))
unnamed: JP3.2, R5.2
unnamed: LVLSHF1.HV1, U2.30 (PD0(RXD))
unnamed: LVLSHF1.HV2, U2.31 (PD1(TXD))
unnamed: JP4.2, Q1.1 (C)
RELE1: JP2.3, U2.24 (PC1(ADC1))
RELE2: JP2.2, U2.25 (PC2(ADC2))
RFID_PW: R1.1, U2.9 (PD5(T1))
RFID_TX: JP4.4, U2.32 (PD2(INT0))
SCL: JP5.3, R7.1, U2.28 (PC5(ADC5/SCL))
SDA: JP5.4, R6.1, U2.27 (PC4(ADC4/SDA))

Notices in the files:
parts and their libraries:
SparkFun-Connectors: Licensing: Creative Commons ShareAlike 4.0 International - https://creativecommons.org/licenses/by-sa/4.0
con-usb: Copyright (C) 2008, Bob Starr
